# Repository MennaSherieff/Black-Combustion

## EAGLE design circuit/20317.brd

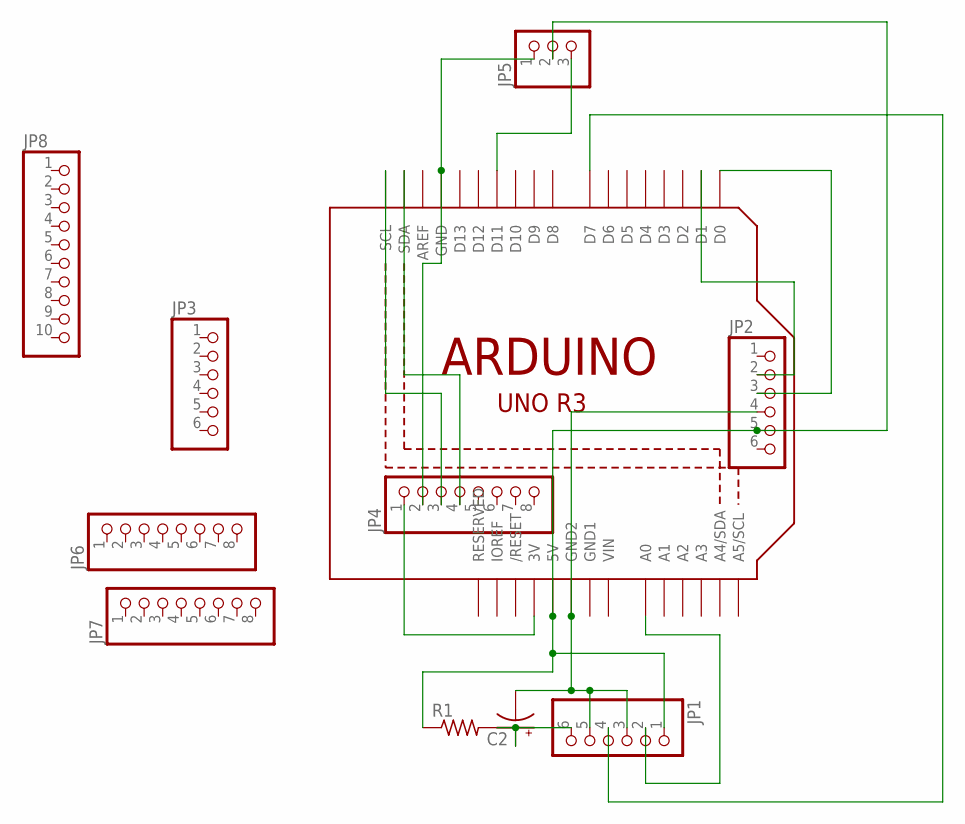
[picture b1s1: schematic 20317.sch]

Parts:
C2: CPOL-USE2.5-7; E2,5-7
JP1, JP2, JP3: PINHD-1X6; 1X06
JP4, JP6, JP7: PINHD-1X8; 1X08
JP5: PINHD-1X3; 1X03
JP8: PINHD-1X10; 1X10
R1: R-US_0207/7; 0207/7
U1: ARDUINOR3-BPLACE

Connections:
GND1: U1.GND1
unnamed: JP5.3, U1.D11
unnamed: JP4.3, U1.SCL
unnamed: JP2.3, U1.D0
unnamed: JP2.2, U1.D1
unnamed: JP4.2, JP5.1, U1.GND
unnamed: JP4.4, U1.SDA
unnamed: JP4.1, U1.3V
unnamed: JP1.2, U1.A0
unnamed: C2.-, JP1.3, JP1.5, JP2.4, U1.GND2
unnamed: JP1.4, U1.D7
unnamed: C2.+, JP1.6, R1.2
unnamed: JP1.1, JP2.5, JP5.2, R1.1, U1.5V
VIN: U1.VIN

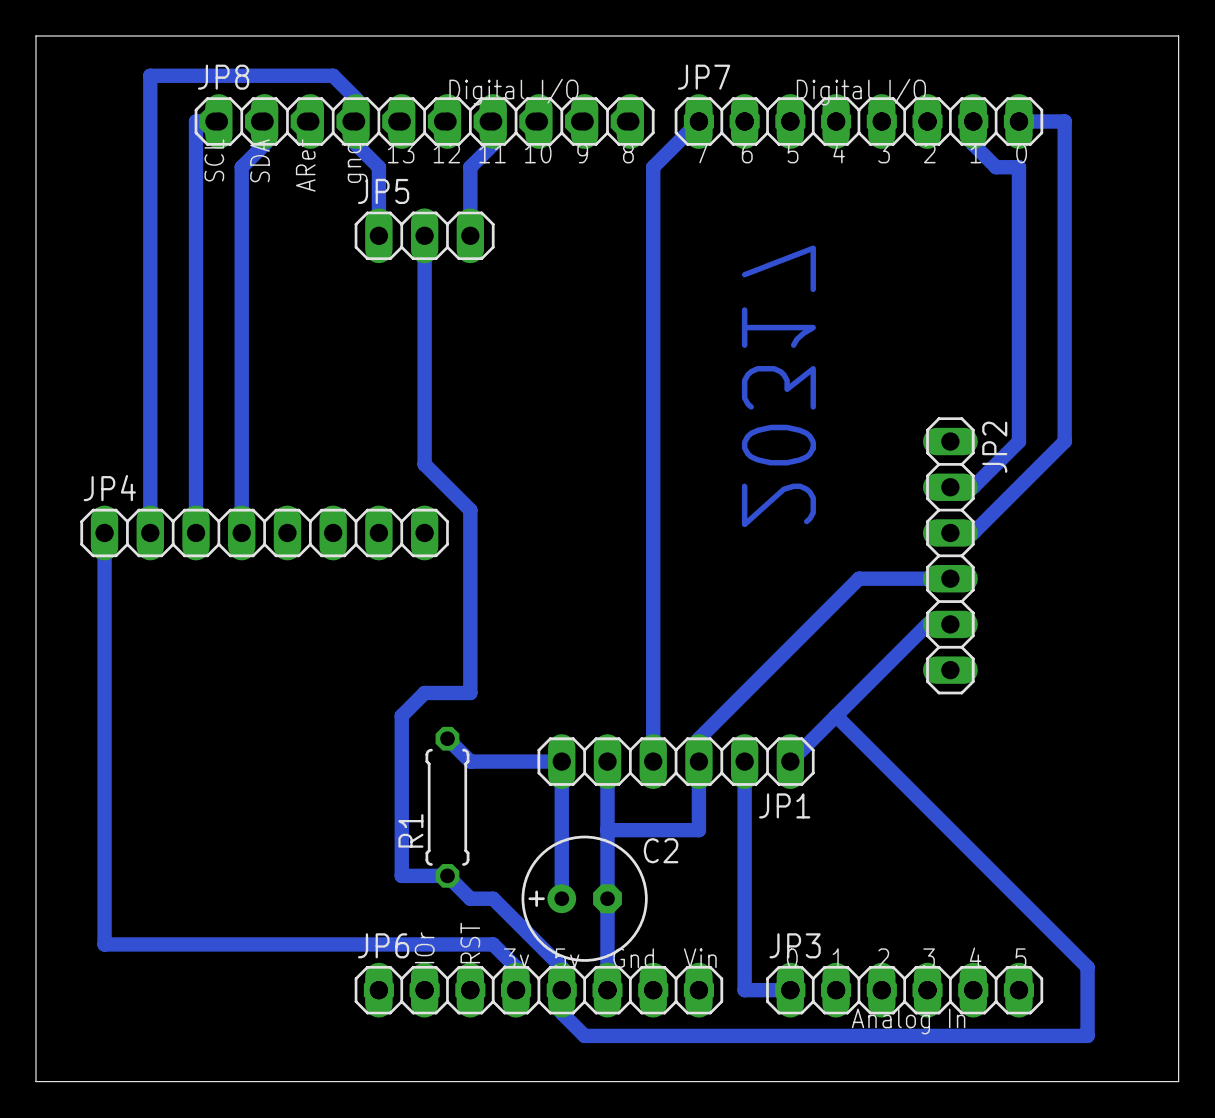
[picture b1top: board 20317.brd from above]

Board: 2 copper layers, 63.5 x 58.1 mm, 11 parts (0 on the bottom side), 12 nets.
